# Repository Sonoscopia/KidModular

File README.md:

# KidModular
(Semi)Modular synthesisers for InSono project (2017 @CCB-Lisbon)

## List of modules
- Oscillator
- Sequencer
- (Active?) Multiples
- DistCV
- PressCV
- Mixer 2ch 

## Acknowledgment
- Henning Karlsen (Arduino UTFT Library)
- Tim Barrass (Mozzi Library)

## Version
Revision B

## List of Changes 
- Oscillator now has 2 Arduinos: a MEGA2560 to handle the screen and UI hardware and a Pro Mini (5V) to handle sound synthesis

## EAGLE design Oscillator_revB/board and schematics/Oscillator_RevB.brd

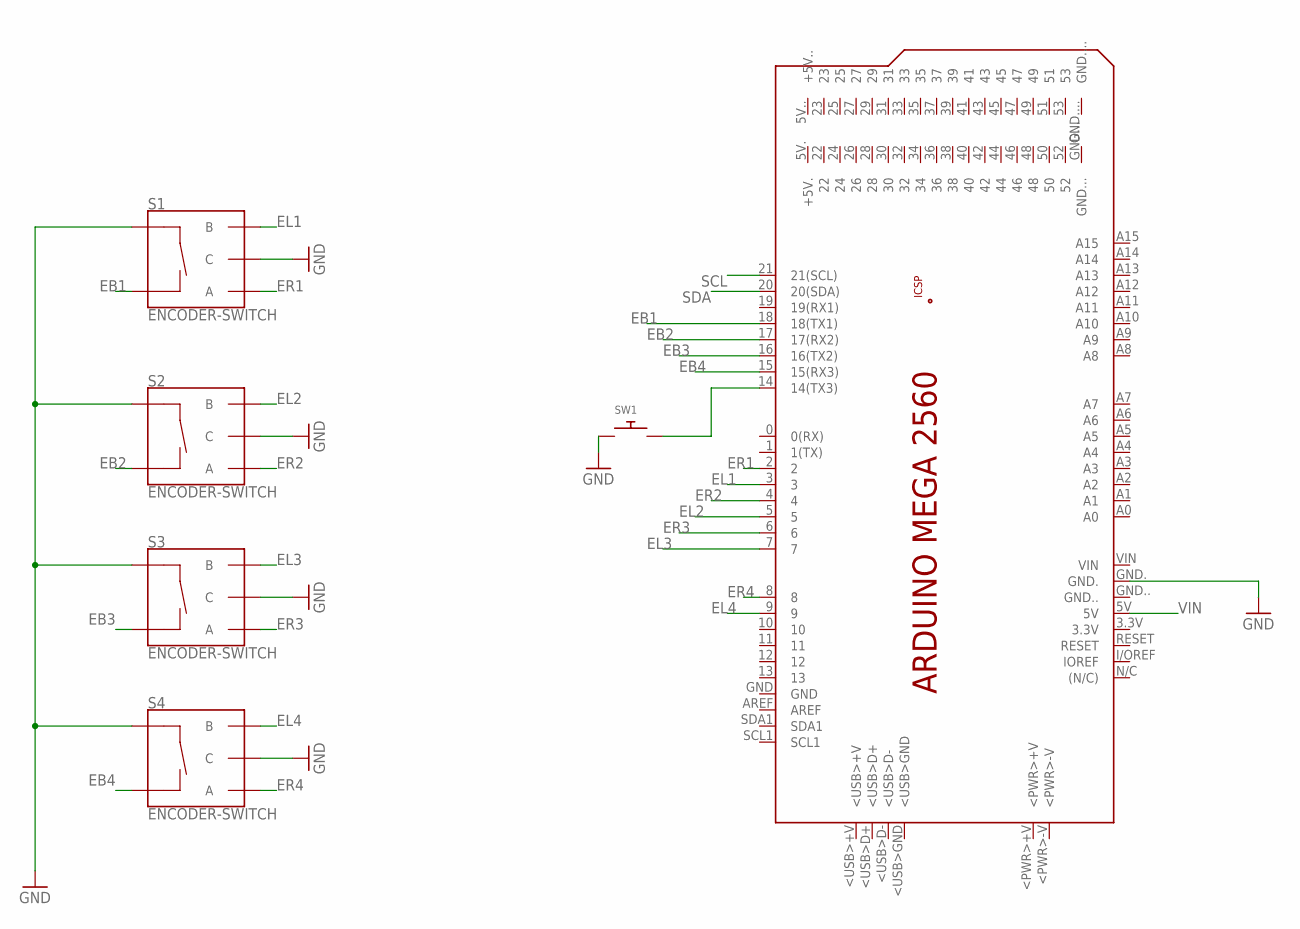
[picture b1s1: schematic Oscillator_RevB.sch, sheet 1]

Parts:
PCB1: ARDUINO_MEGA2560
S1, S2, S3, S4: ENCODER-SWITCH; ROTARY_ENC_PLAIN
SW1: SWITCH_PUSHBUTTONEVQ-PE; TACT_PANA-EVQ

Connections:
EB1: PCB1.18 (18(TX1)), S1.SW-
EB2: PCB1.17 (17(RX2)), S2.SW-
EB3: PCB1.16 (16(TX2)), S3.SW-
EB4: PCB1.15 (15(RX3)), S4.SW-
EL1: PCB1.3, S1.B
EL2: PCB1.5, S2.B
EL3: PCB1.7, S3.B
EL4: PCB1.9, S4.B
ER1: PCB1.2, S1.A
ER2: PCB1.4, S2.A
ER3: PCB1.6, S3.A
ER4: PCB1.8, S4.A
GND: PCB1.GND., S1.C, S1.SW+, S2.C, S2.SW+, S3.C, S3.SW+, S4.C, S4.SW+, SW1.P$1; also elsewhere on the board
unnamed: PCB1.14 (14(TX3)), SW1.P$2
SCL: PCB1.21 (21(SCL)); also elsewhere on the board
SDA: PCB1.20 (20(SDA)); also elsewhere on the board
VIN: PCB1.5V; also elsewhere on the board

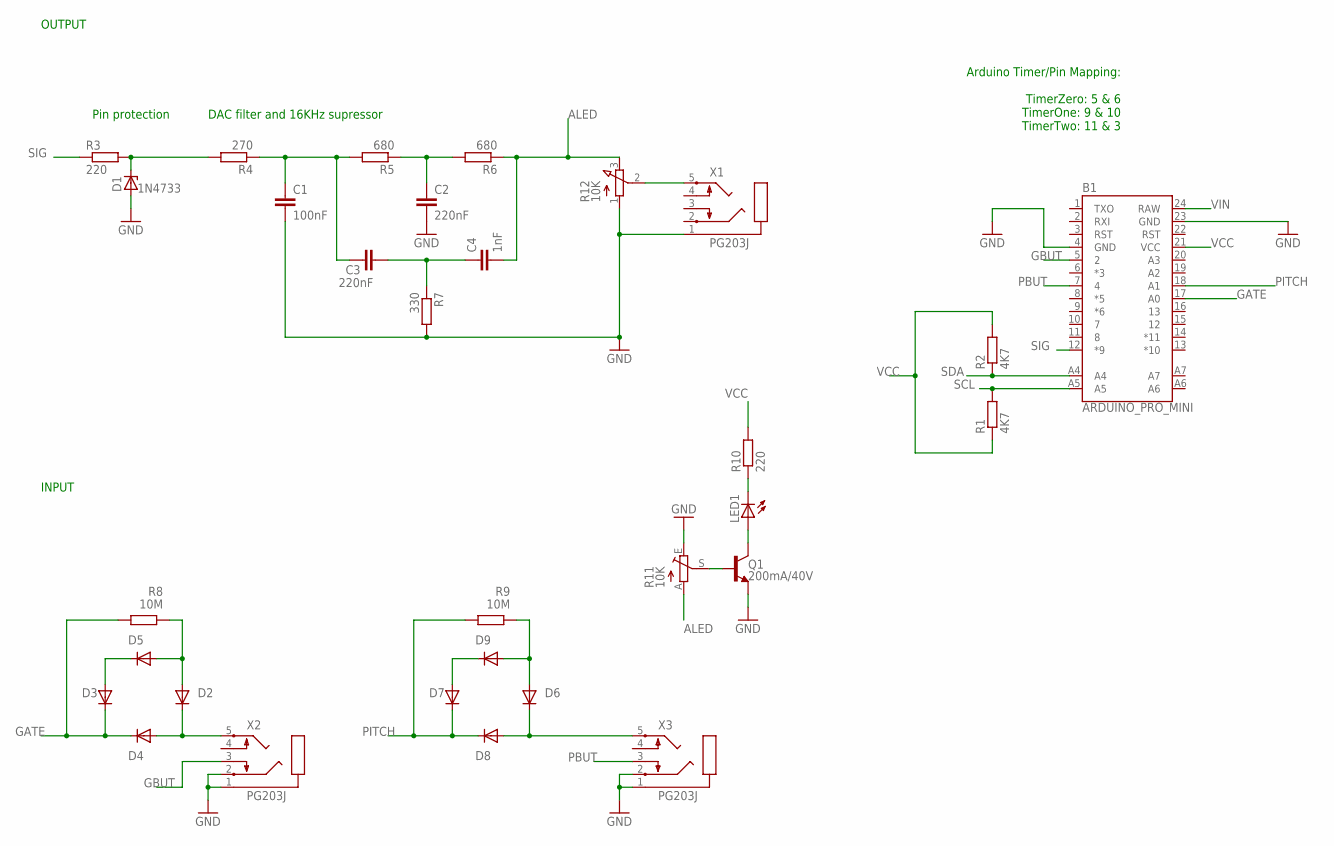
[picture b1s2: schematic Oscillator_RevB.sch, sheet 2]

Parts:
B1: ARDUINO_PRO_MINI
C1: 100nF; C5B3
C2, C3: 220nF; C7.5B6
C4: 1nF; C5B3
D1: 1N4733; DO34Z7
D2, D3, D4, D5, D6, D7, D8, D9: 1N4004; DO41-10
LED1: LED5MM
Q1: 200mA/40V; TO-92
R1, R2: 4K7; 0204/7
R3, R10: 220; 0204/7
R4: 270; 0204/7
R5, R6: 680; 0204/7
R7: 330; 0204/7
R8, R9: 10M; 0204/7
R11: 10K; LI10
R12: 10K; 3RP/1610N
X1, X2, X3: PG203J

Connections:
ALED: C4.2, R6.1, R11.A, R12.3 (E)
GATE: B1.17 (A0), D3.C, D4.C, R8.1
GBUT: B1.5 (2), X2.3
GND: B1.4 (GND), B1.23 (GND), C1.2, C2.2, D1.A, Q1.1 (E), R7.2, R11.E, R12.1 (A), X1.1, X2.1, X2.2, X3.1, X3.2; also elsewhere on the board
unnamed: LED1.A, Q1.3 (C)
unnamed: LED1.K (C), R10.1
unnamed: D1.C, R3.2, R4.2
unnamed: C1.1, C3.1, R4.1, R5.2
unnamed: C2.1, R5.1, R6.2
unnamed: C3.2, C4.1, R7.1
unnamed: D2.C, D4.A, X2.5
unnamed: D6.A, D9.A, R9.2
unnamed: D2.A, D5.A, R8.2
unnamed: D3.A, D5.C
unnamed: D7.A, D9.C
unnamed: Q1.2 (B), R11.S
unnamed: R12.2 (S), X1.5
PBUT: B1.7 (4), X3.3
PITCH: B1.18 (A1), D7.C, D8.C, R9.1
PIT_IN: D6.C, D8.A, X3.5
SCL: B1.A5, R1.2; also elsewhere on the board
SDA: B1.A4, R2.1; also elsewhere on the board
SIG: B1.12 (*9), R3.1
VCC: B1.21 (VCC), R1.1, R2.2, R10.2
VIN: B1.24 (RAW); also elsewhere on the board

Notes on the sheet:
Arduino Timer/Pin Mapping: TimerZero: 5 & 6 TimerOne: 9 & 10 TimerTwo: 11 & 3
Pin protection
DAC filter and 16KHz supressor
OUTPUT
INPUT

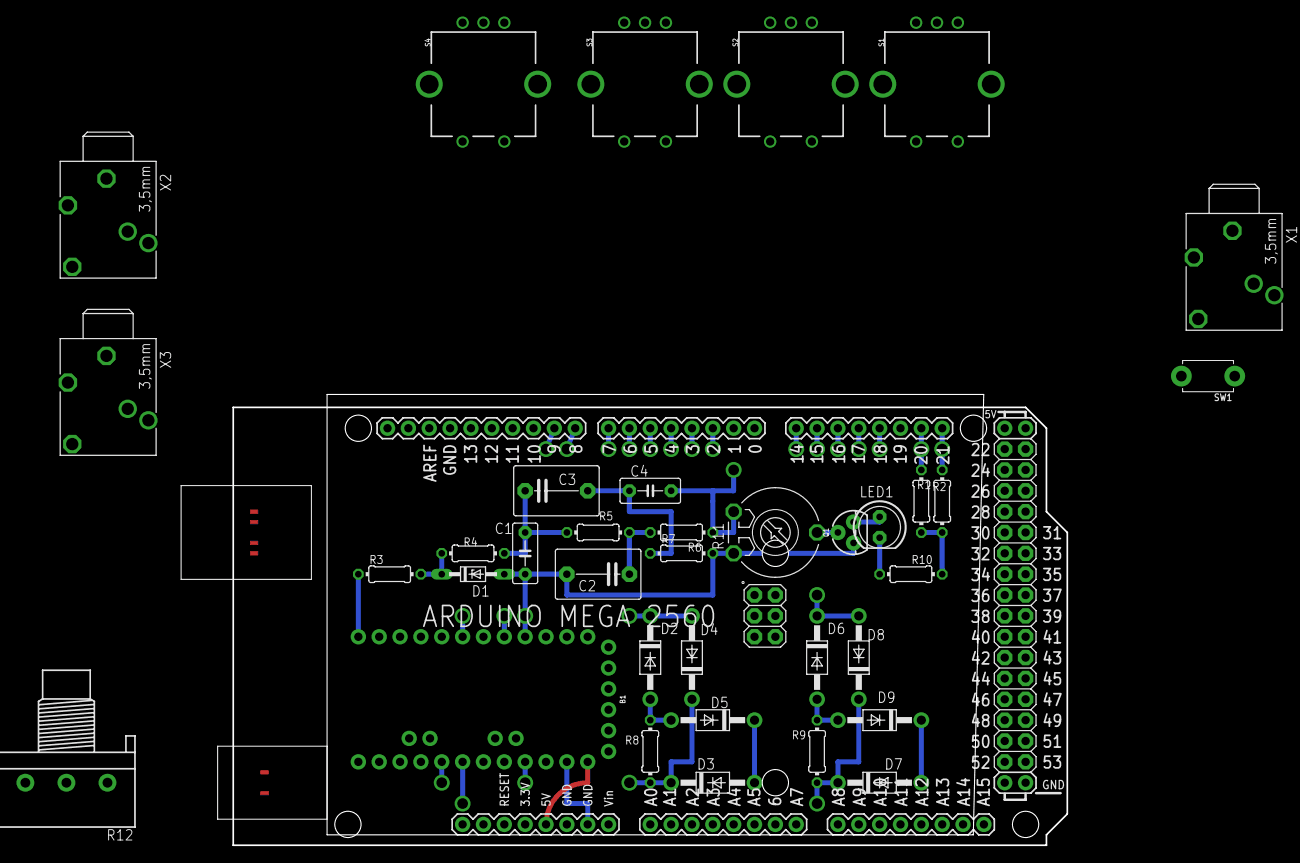
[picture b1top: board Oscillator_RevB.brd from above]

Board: 4 copper layers, 101.6 x 54.9 mm, 37 parts (0 on the bottom side), 38 nets.

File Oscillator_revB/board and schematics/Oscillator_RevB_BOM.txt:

Partlist exported from C:/Users/tiago/Documents/GitHub/KidModular/Oscillator_revB/board and schematics/Oscillator_RevB.sch at 03-04-2018 20:12

Qty Value            Device                  Package          Parts                          Description                                                                                                                                                                                                                
1                    LED5MM                  LED5MM           LED1                           LED                                                                                                                                                                                                                        
1                    SWITCH_PUSHBUTTONEVQ-PE TACT_PANA-EVQ    SW1                            Buttons                                                                                                                                                                                                                    
1   100nF            C5/3                    C5B3             C1                             CAPACITOR                                                                                                                                                                                                                  
1   10K              3RP/1610N               3RP/1610N        R12                            16mm Potentiometer one level                                                                                                                                                                                               
1   10K              TRIM_EU-LI10            LI10             R11                            POTENTIOMETER                                                                                                                                                                                                              
2   10M              R-EU_0204/7             0204/7           R8, R9                         RESISTOR, European symbol                                                                                                                                                                                                  
1   120              R-EU_0204/7             0204/7           R10                            RESISTOR, European symbol                                                                                                                                                                                                  
8   1N4004           1N4004                  DO41-10          D2, D3, D4, D5, D6, D7, D8, D9 DIODE                                                                                                                                                                                                                      
1   1N4733           ZENER-DIODEDO34-7       DO34Z7           D1                             Z-Diode                                                                                                                                                                                                                    
1   1nF              C5/3                    C5B3             C4                             CAPACITOR                                                                                                                                                                                                                  
1   200mA/40V        TRANS_NPN-2N3904        TO-92            Q1                             NPN transistor                                                                                                                                                                                                             
1   220              R-EU_0204/7             0204/7           R3                             RESISTOR, European symbol                                                                                                                                                                                                  
2   220nF            C7.5/6                  C7.5B6           C2, C3                         CAPACITOR                                                                                                                                                                                                                  
1   270              R-EU_0204/7             0204/7           R4                             RESISTOR, European symbol                                                                                                                                                                                                  
1   330              R-EU_0204/7             0204/7           R7                             RESISTOR, European symbol                                                                                                                                                                                                  
2   4K7              R-EU_0204/7             0204/7           R1, R2                         RESISTOR, European symbol                                                                                                                                                                                                  
2   680              R-EU_0204/7             0204/7           R5, R6                         RESISTOR, European symbol                                                                                                                                                                                                  
1   ARDUINO_MEGA2560 ARDUINO_MEGA2560        ARDUINO_MEGA2560 PCB1                           Device for representing an Arduino Mega 2560 board with a footprint in an EAGLE design. Created by Dave Young for Element14. More EAGLE documentation at: http://www.element14.com/community/community/knode/cadsoft_eagle 
1   ARDUINO_PRO_MINI ARDUINO_PRO_MINI        ARDUINO_PRO_MINI B1                             SparkFun Pro Mini                                                                                                                                                                                                          
4   ENCODER-SWITCH   ENCODER-SWITCH          ROTARY_ENC_PLAIN S1, S2, S3, S4                 Rotary Encoder w/ Select Switch                                                                                                                                                                                            
3   PG203J           PG203J                  PG203J           X1, X2, X3                     MIC/HEADPHONE JACK

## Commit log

2017-01-24 Add gitignore: DS_Store and all folders starting with _ (underscore)
2017-01-24 OSCILLATOR: first sketch
2017-01-25 First working example of Sinewave+UTFT. Ussing Direct Digital Synthesis method to generate a sinewave
2017-01-25 clean up
2017-01-25 moved wavetable to header file
2017-01-25 cleaned up code
2017-01-26 added simple scope example
2017-01-26 Added Sequencer code (first sketch)
2017-01-27 Added encoder example
2017-01-27 moved LCD_Scope_example to examples folder
2017-01-27 removed old files
2017-01-27 upload utilities folder
2017-01-27 cleand utils
2017-01-27 added utils
2017-01-27 minor changes
2017-01-27 added bpm and numSteps control/draw
2017-01-28 changed code to suit my purpose
2017-01-28 implemented duration edit with encder
2017-01-28 implemented shapeDraw
2017-01-28 Added Sequencer example
2017-01-28 added bpm control
2017-01-28 simplified the algorithm
2017-01-28 Fast and efficient sequencer
2017-01-29 organizing to classes
2017-01-29 Fully functional prototype
2017-01-29 fast frequency control
2017-01-29 simple sinewave generator
2017-01-29 optimized variable types
2017-01-29 faster frequency control
2017-01-29 fine sweep frequency control
2017-01-29 cleanup
2017-01-29 added basic screen class for LCD
2017-01-30 oscillator+scope example
2017-01-30 first functional prototype
2017-01-30 added example of how to use osc freq controlled by encoder without interrupts
2017-01-30 added control class w/ no errors but not working properly
2017-01-30 removed control class. Freq control is working w/ encoder
2017-01-30 tuned Routine Rates
2017-01-30 implemnted label display
2017-01-30 implementd freq multipliers
2017-01-30 freq display fix
2017-01-30 restructured screen display
2017-01-30 changed screen.freq to pointer of dfreq, this way there is no need to update or resend value to screen object
2017-01-30 added screen mode: scope/envelope
2017-02-04 added oscil example
2017-02-04 updated Oscillator
2017-02-06 v.0.1.0 first version mounted on the box
2017-02-06 defined controls
2017-02-06 went back
2017-02-07 added Gate output
2017-02-07 added Pitch output
2017-02-07 version 0.1.1
2017-02-07 fix pitch output to conform to 1V/oct fro 0 to 5V
2017-02-08 fixed bug when changing numSteps
2017-02-08 crude implementation of Gate and Pitch CV
2017-06-15 DistCV v0.1
    sonar distance to CV
2018-03-15 Revert "Updated README"
    This reverts commit 52ad4cd92a5b1773811de0aa1583ee13cdd0dcb1.
2018-03-16 Added Examples
    - Arduino to Arduino via I2C (basic)
    - Arduino to Arduino via I2C (while using Mozzi)
    - Menu Button edge detection
    - Passing structures to functions
    - Passing structures to class methods
2018-03-16 Moved Oscillator to Oscillator_revA
    this will only be kept while revB is not ready
2018-03-16 Oscillator revB first upload
    - draw and select top menu
2018-03-16 improved example
    now able to reference struct object to class object
2018-03-16 Revert "improved example"
    This reverts commit 4a96455132955facff672db9a358db9379d91158.
2018-03-16 improved example
    now able to reference struct object from class object
2018-03-16 Oscillator change
    placed all synthesis variables in a struct inside Parameters.h
    then referencing the struct object from other classes
2018-03-16 Oscillator: added bottom menu
2018-03-16 added hardware testers
2018-03-16 Added encoder example with tidy class
2018-03-21 added EncoderHandler class
    this handles encoder behaviour
2018-03-21 Moved project to ATMEL Studio
    also improved classes and refactored code
2018-03-22 first working skeleton
2018-03-22 Managed to read encoder data from Control object
2018-03-22 Managed to read encoder from EncoderHandler
2018-03-23 Managed to set parameters.data from EncoderHandler
2018-03-23 implemented clip() function to limit parameter setting in EncoderHandler
2018-03-23 Managed to draw from Menu object
2018-03-23 added menu button reading
2018-03-23 implemented top and bottom menu drawing
2018-03-23 implemented whole menu display
2018-03-23 Implemente parameter control (still with some bugs)
2018-03-24 Improved EncoderHandler
2018-03-24 replaced Encoder library by Rotary and added TimerOne as well
    encoders weren't properly read because UTFT was hogging the cpu
    so encoders are now read in a ISR in Timer1
    see examples/testTimerOneEncodersUTFT
2018-03-24 successfull implementation of Rotary and TimerOne
    TO DO (next):
    - send data via I2C
2018-03-25 Implemented 1st I2C prototype
2018-03-25 Changed parameter val types from byte to uint8_t and int8_t
2018-03-25 refactored Parameter types and relative functions
2018-03-25 added example to convert one int to two bytes and back again
2018-03-25 fixed issues caused by refactoring parameters variable types
2018-03-25 added hardware tester for I2C messages
2018-03-25 finished implementing I2C on sender (controller)
2018-03-29 updated DistCV to version 0.2
    several fixes and improvementes
2018-03-29 changed pins due to timers
2018-03-31 Updated DistCV code
    included an average sensor value
2018-04-02 fixed wrong wire.send message
2018-04-02 1st working example of I2C using twi_nonblock
2018-04-02 Fixed I2C to only send data on parameter changes
2018-04-02 changed mark for no sent message
2018-04-02 first working synth draft
2018-04-15 schematic and BOM upload

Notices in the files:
parts and their libraries:
SparkFun-Boards: Licensing: Creative Commons ShareAlike 4.0 International - https://creativecommons.org/licenses/by-sa/4.0
